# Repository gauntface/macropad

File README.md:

# Macropad

The PCB used the following libs:

- https://github.com/perigoso/keyswitch-kicad-library
- https://github.com/gauntface/kicad-libraries

## Arduino

1. Install the Arduino IDE
    1. Fedora should use flathub to avoid [this issue](https://github.com/arduino/Arduino/issues/11150)
        ```
        flatpak remote-add --if-not-exists flathub https://flathub.org/repo/flathub.flatpakrepo
        flatpak install flathub cc.arduino.arduinoide
        ```
1. Install the following libraries under `Tools > Manage Libraries`:
    - HID-Project
    - Adafruit GFX Library
    - Adafruit SSD1306
1. Install board in Arduino - [see Sparkfuns guide for pro micro](https://learn.sparkfun.com/tutorials/pro-micro--fio-v3-hookup-guide/installing-mac--linux)

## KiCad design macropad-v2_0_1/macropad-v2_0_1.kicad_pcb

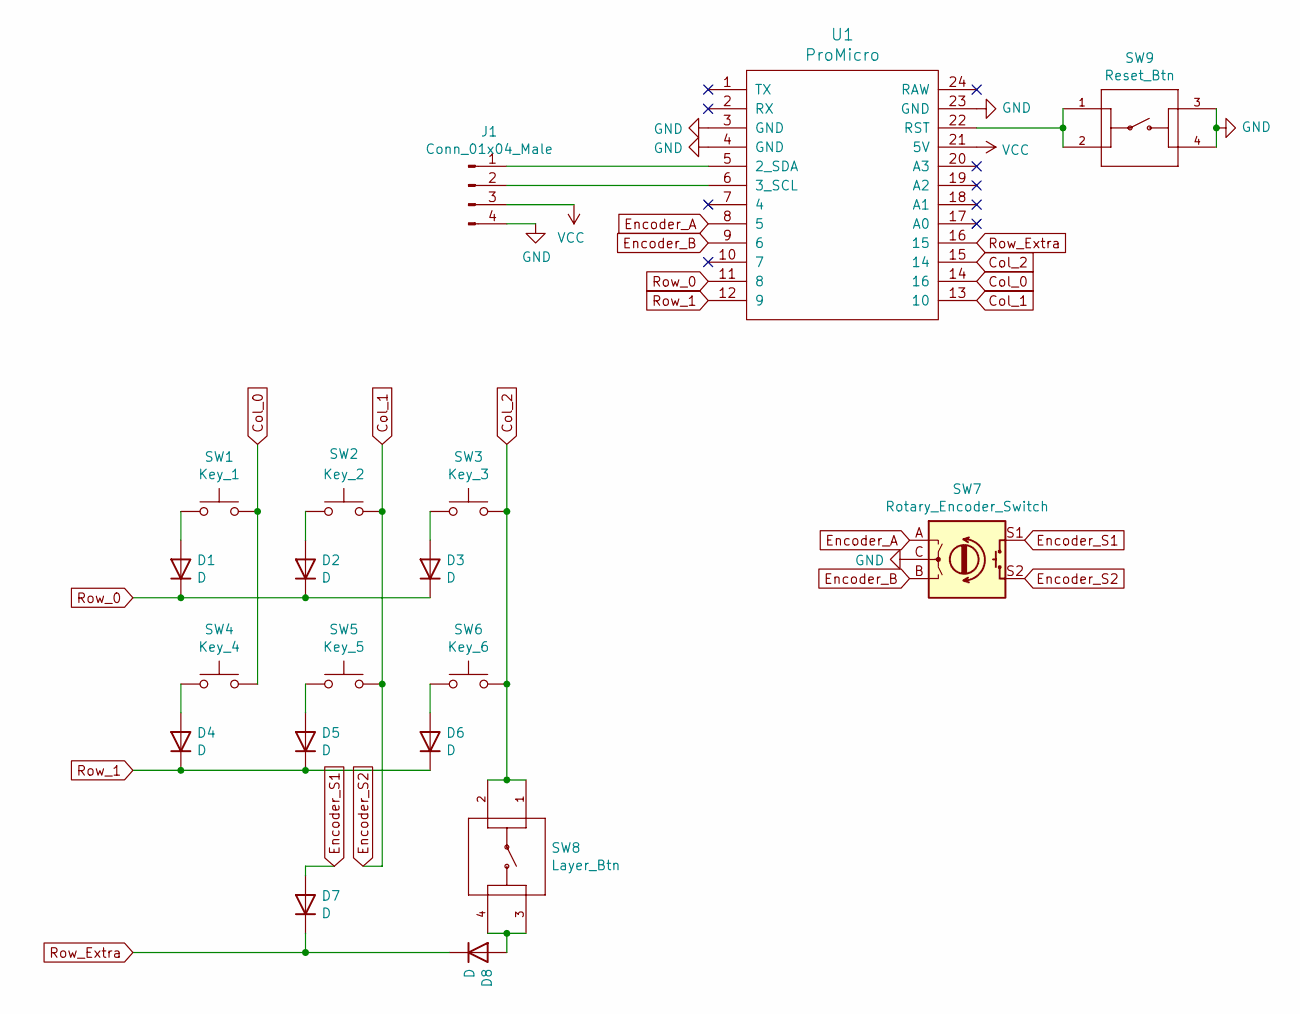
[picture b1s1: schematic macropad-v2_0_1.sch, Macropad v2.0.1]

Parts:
D1, D2, D3, D4, D5, D6, D7, D8: D; D_A-405_P7.62mm_Horizontal
J1: Conn_01x04_Male; Screen_38x12mm_JMD0_91_a
SW1: Key_1; SW_Hotswap_Kailh
SW2: Key_2; SW_Hotswap_Kailh
SW3: Key_3; SW_Hotswap_Kailh
SW4: Key_4; SW_Hotswap_Kailh
SW5: Key_5; SW_Hotswap_Kailh
SW6: Key_6; SW_Hotswap_Kailh
SW7: Rotary_Encoder_Switch; ACZ11BRXE
SW8: Layer_Btn; SW_1825910-6-4
SW9: Reset_Btn; SW_1825910-6-4
U1: ProMicro

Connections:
Col_0: SW1.2, SW4.2, U1.14 (16)
Col_1: SW2.2, SW5.2, SW7.S2, U1.13 (10)
Col_2: SW3.2, SW6.2, SW8.1, SW8.2, U1.15 (14)
Encoder_A: SW7.A, U1.8 (5)
Encoder_B: SW7.B, U1.9 (6)
Encoder_S1: D7.2 (A), SW7.S1
GND: J1.4, SW7.C, SW9.3, SW9.4, U1.3 (GND), U1.4 (GND), U1.23 (GND)
unnamed: D1.2 (A), SW1.1
unnamed: D2.2 (A), SW2.1
unnamed: D3.2 (A), SW3.1
unnamed: D4.2 (A), SW4.1
unnamed: D5.2 (A), SW5.1
unnamed: D6.2 (A), SW6.1
unnamed: D8.2 (A), SW8.3, SW8.4
unnamed: J1.1, U1.5 (2_SDA)
unnamed: J1.2, U1.6 (3_SCL)
unnamed: SW9.1, SW9.2, U1.22 (RST)
Row_0: D1.1 (K), D2.1 (K), D3.1 (K), U1.11 (8)
Row_1: D4.1 (K), D5.1 (K), D6.1 (K), U1.12 (9)
Row_Extra: D7.1 (K), D8.1 (K), U1.16 (15)
VCC: J1.3, U1.21 (5V)

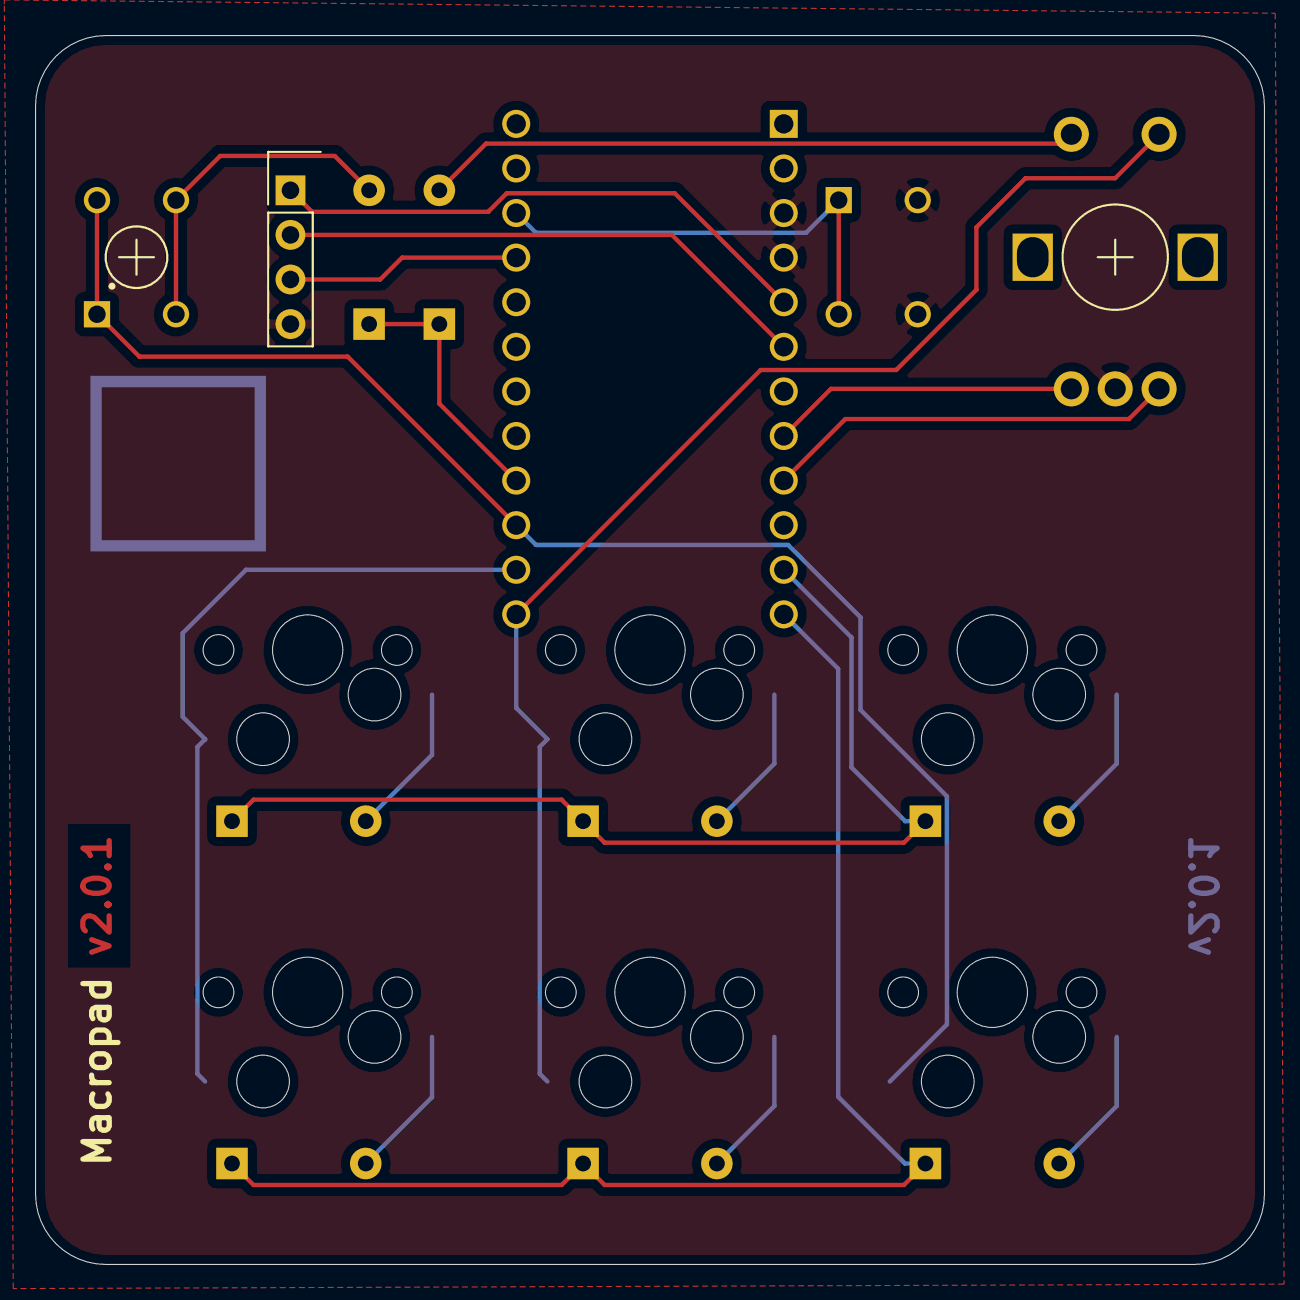
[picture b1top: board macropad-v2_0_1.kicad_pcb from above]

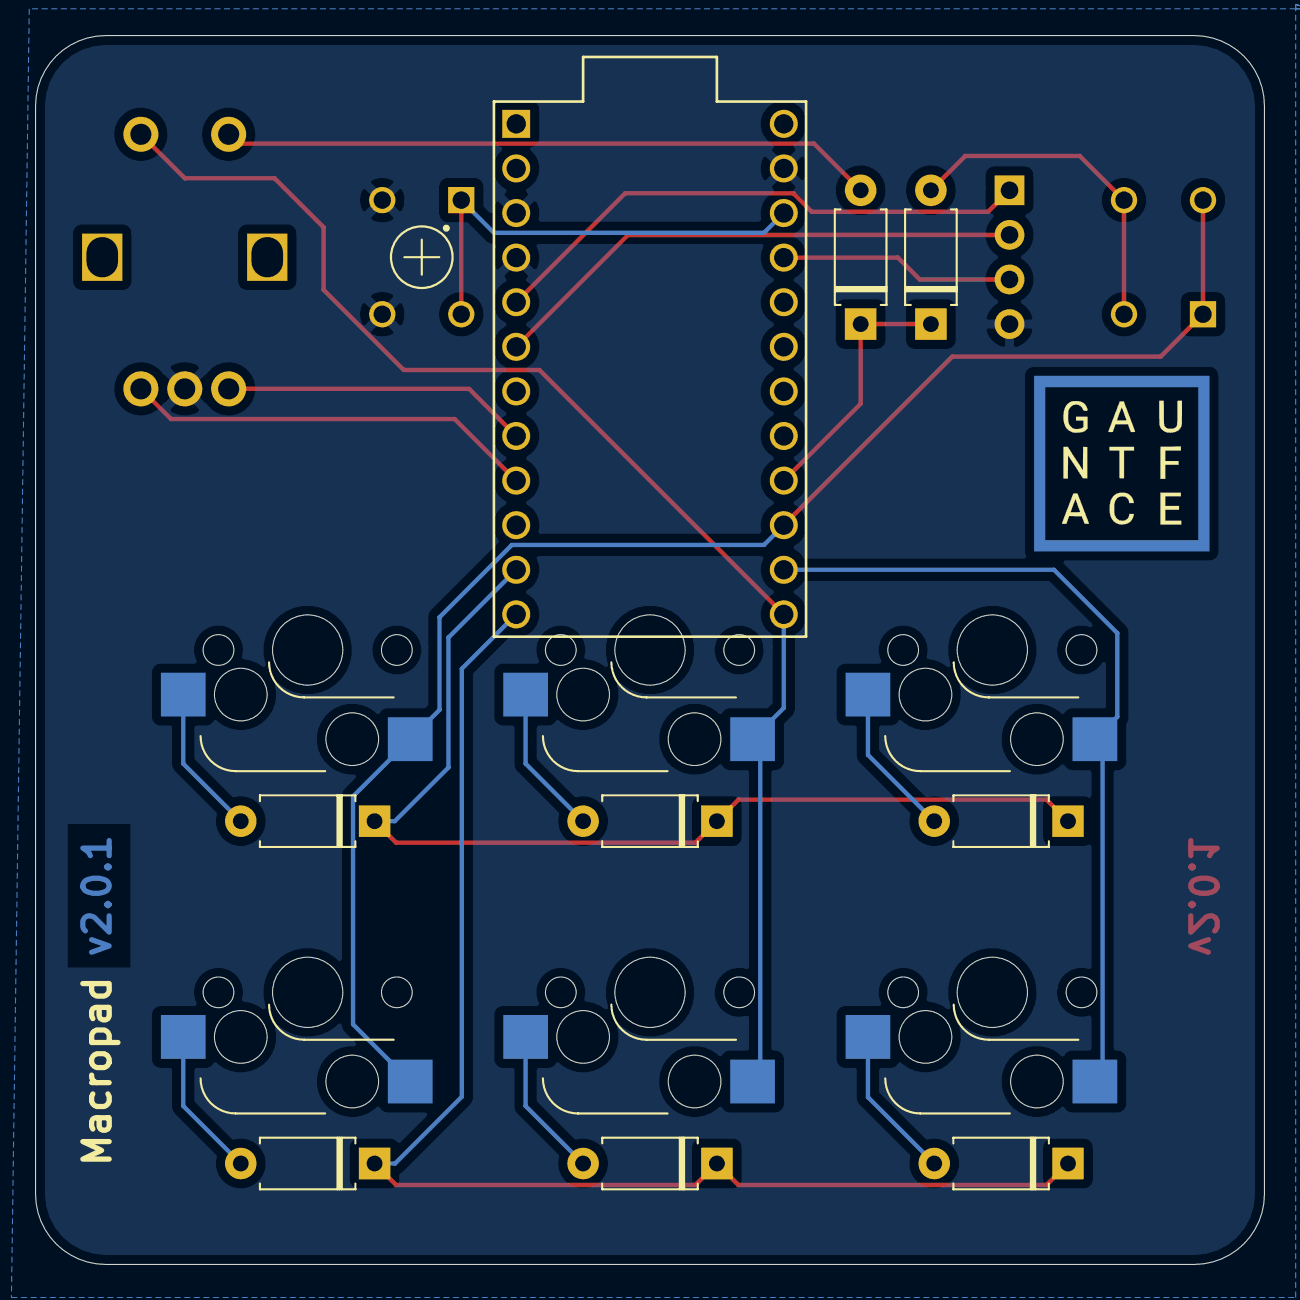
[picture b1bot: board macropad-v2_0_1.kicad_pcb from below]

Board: 2 copper layers, 70.0 x 70.0 mm, 20 parts (11 on the bottom side), 21 nets.

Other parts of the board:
Ref**: Val**; gauntface-logo

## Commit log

2021-03-22 Adding README
2021-04-11 Started coding up the keyboard matrix and finished v2
2021-04-11 Adding update plot files
2021-04-23 Adding working arduino code and second rev of schematic
2021-04-23 Adding paths to schematic
2021-04-25 Adding plots
2021-05-31 Adding kicad and updating layer logic
2022-06-03 Updating linux layer to support google meet and zoom
2022-09-25 Adding mouse jiggler and screen commands for layer change
2022-09-27 Adding short timeout period
2022-10-10 Start fresh
2022-10-10 Scaffold project
2022-10-10 Adding the first reading from a serial port
